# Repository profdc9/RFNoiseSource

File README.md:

This is a RF noise source based on a cheaply available 2SC3356 Bipolar Transistor by Daniel L. Marks, KW4TI.  This is an experiment to see how much noise a reversed biased emitter-base can create.

The PCB design is distributed under the Creative Commons Shared Alike Attribution (CC-BY-SA 4.0) license.

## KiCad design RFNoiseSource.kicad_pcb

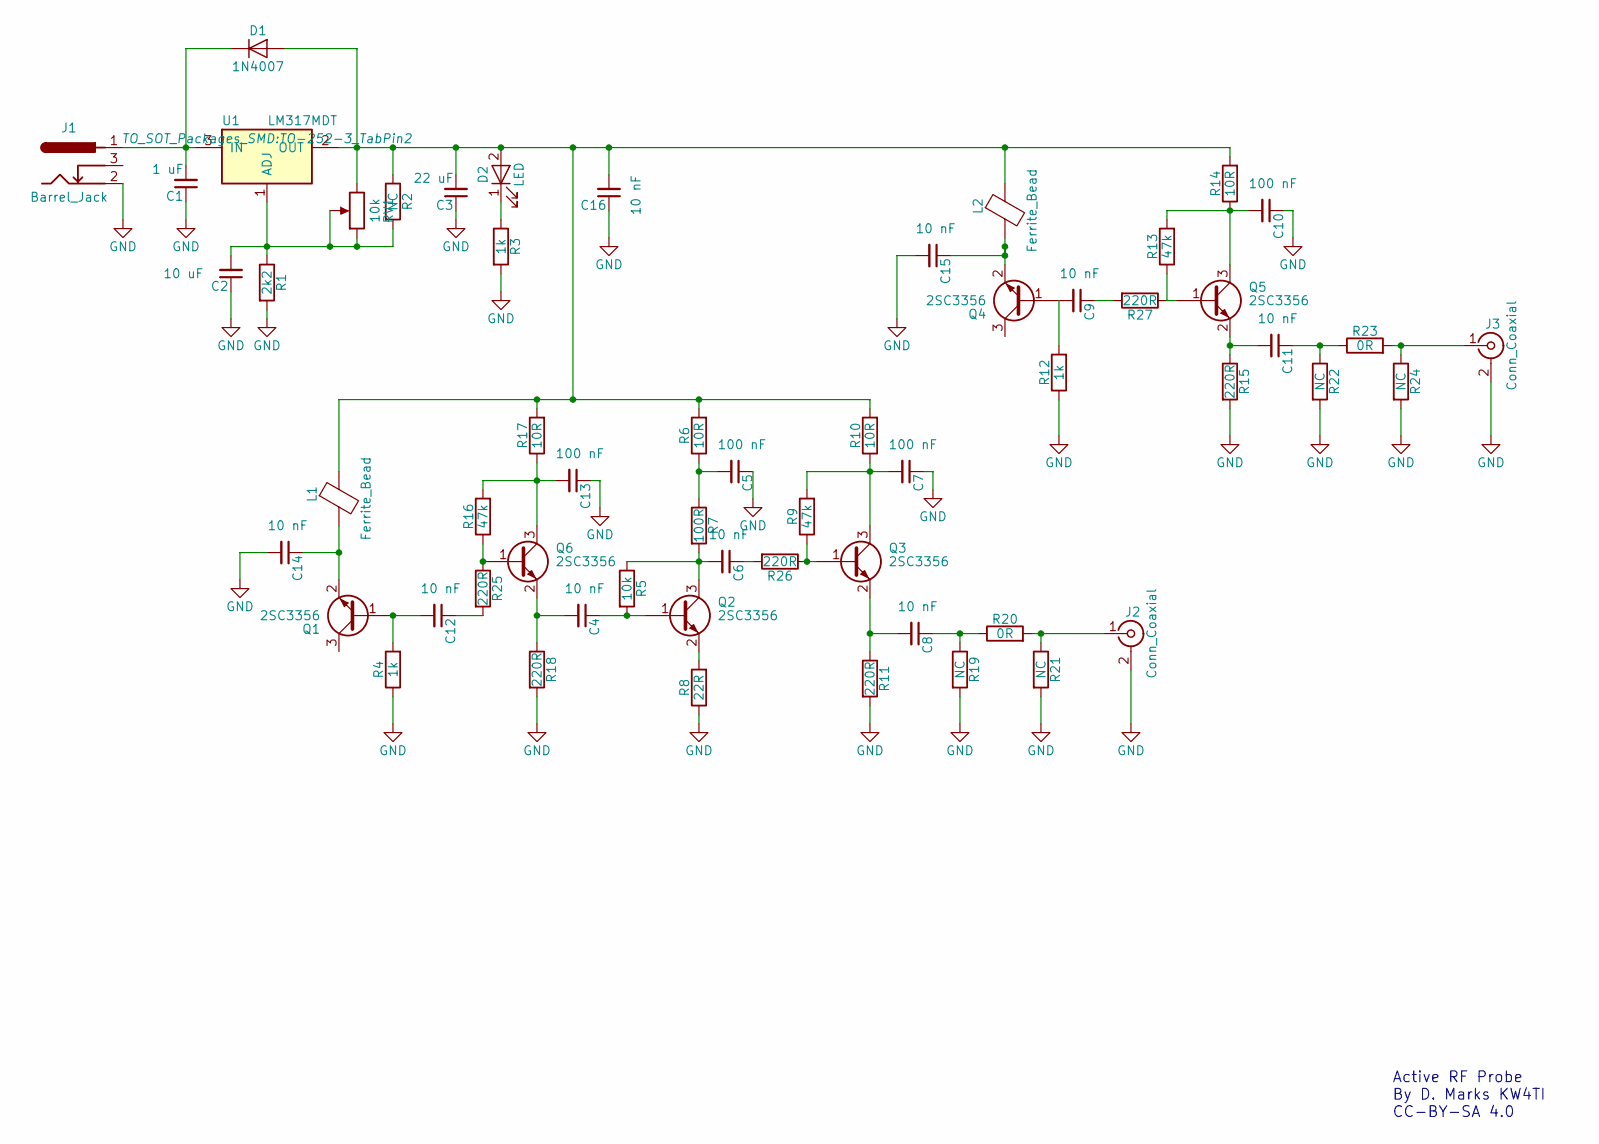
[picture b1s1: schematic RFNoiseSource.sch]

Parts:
C1: 1 uF; C_0805_HandSoldering; LCSC C28323
C2: 10 uF; C_0805_HandSoldering; LCSC C15850
C3: 22 uF; C_0805_HandSoldering; LCSC C45783
C4, C6, C8, C9, C11, C12, C14, C15, C16: 10 nF; C_0805_HandSoldering; LCSC C1710
C5, C7, C10, C13: 100 nF; C_0805_HandSoldering; LCSC C49678
D1: 1N4007; D_SMA_Handsoldering; LCSC C95872
D2: LED; LED_0805_HandSoldering; LCSC C2296
J1: Barrel_Jack; BARREL_JACK
J2, J3: Conn_Coaxial; Amphenol_RF_SMA_132289
L1, L2: Ferrite_Bead; L_0805_HandSoldering; LCSC C1017
Q1, Q2, Q3, Q4, Q5, Q6: 2SC3356; SOT-23; LCSC C9659
R1: 2k2; R_0805_HandSoldering; LCSC C17520
R2, R19, R21, R22, R24: NC; R_0805_HandSoldering
R3, R4, R12: 1k; R_0805_HandSoldering; LCSC C17513
R5: 10k; R_0805_HandSoldering; LCSC C17414
R6, R10, R14, R17: 10R; R_0805_HandSoldering; LCSC C17415
R7: 100R; R_0805_HandSoldering; LCSC C17408
R8: 22R; R_0805_HandSoldering; LCSC C17561
R9, R13, R16: 47k; R_0805_HandSoldering; LCSC C17713
R11, R15, R18, R25, R26, R27: 220R; R_0805_HandSoldering; LCSC C17557
R20, R23: 0R; R_0805_HandSoldering; LCSC C17477
RV1: 10k; Potentiometer_Triwood_RM-065
U1: LM317MDT; TO-252-3_TabPin2; LCSC C75510

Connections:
GND: C1.1, C2.1, C3.1, C5.1, C7.1, C10.1, C13.1, C14.2, C15.2, C16.1, J1.2, J2.2 (Ext), J3.2 (Ext), R1.2, R3.2, R4.1, R8.1, R11.2, R12.1, R15.2, R18.2, R19.2, R21.2, R22.2, R24.2
unnamed: C1.2, D1.1 (K), J1.1, U1.3 (IN)
unnamed: C2.2, R1.1, R2.2, RV1.1, RV1.2, U1.1 (ADJ)
unnamed: C4.1, Q2.1 (B), R5.2
unnamed: C4.2, Q6.2 (E), R18.1
unnamed: C5.2, R6.1, R7.1
unnamed: C6.1, R26.2
unnamed: C6.2, Q2.3 (C), R5.1, R7.2
unnamed: C7.2, Q3.3 (C), R9.2, R10.1
unnamed: C8.1, R19.1, R20.1
unnamed: C8.2, Q3.2 (E), R11.1
unnamed: C9.1, R27.2
unnamed: C9.2, Q4.1 (B), R12.2
unnamed: C10.2, Q5.3 (C), R13.2, R14.1
unnamed: C11.1, R22.1, R23.1
unnamed: C11.2, Q5.2 (E), R15.1
unnamed: C12.1, R25.2
unnamed: C12.2, Q1.1 (B), R4.2
unnamed: C13.2, Q6.3 (C), R16.2, R17.1
unnamed: C14.1, L1.2, Q1.2 (E)
unnamed: C15.1, L2.2, Q4.2 (E)
unnamed: C3.2, C16.2, D1.2 (A), D2.2 (A), L1.1, L2.1, R2.1, R6.2, R10.2, R14.2, R17.2, RV1.3, U1.2 (OUT)
unnamed: D2.1 (K), R3.1
unnamed: J2.1 (In), R20.2, R21.1
unnamed: J3.1 (In), R23.2, R24.1
unnamed: Q2.2 (E), R8.2
unnamed: Q3.1 (B), R9.1, R26.1
unnamed: Q5.1 (B), R13.1, R27.1
unnamed: Q6.1 (B), R16.1, R25.1

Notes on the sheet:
Active RF Probe By D. Marks KW4TI CC-BY-SA 4.0

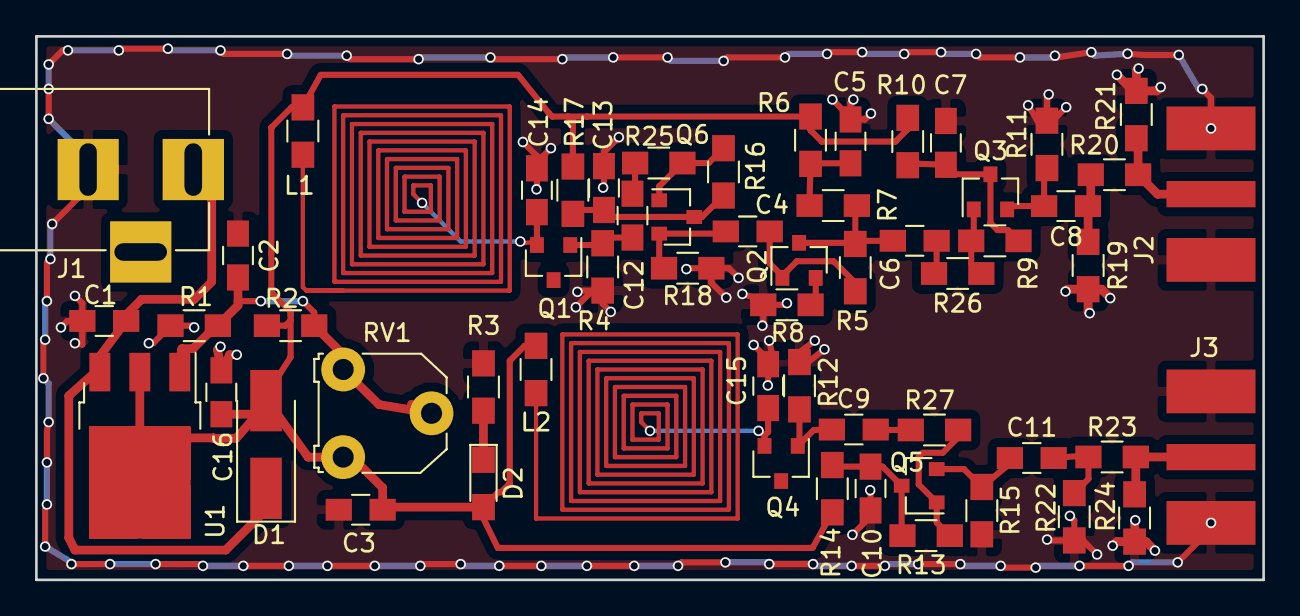
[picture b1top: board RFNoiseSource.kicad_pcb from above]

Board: 2 copper layers, 70.0 x 31.0 mm, 58 parts (0 on the bottom side), 29 nets.

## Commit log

2020-04-29 Added LCSC part numbers, added cutout notched, added series base resistors to emitter followers
2020-05-07 Changed regulator
